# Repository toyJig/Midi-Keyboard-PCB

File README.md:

# Midi-Keyboard-PCB
A simple small MIDI Keyboard PCB designed for Half Life Hack Club with buttons, sliders, potentiometer and mcu.

View the PCB Here!:

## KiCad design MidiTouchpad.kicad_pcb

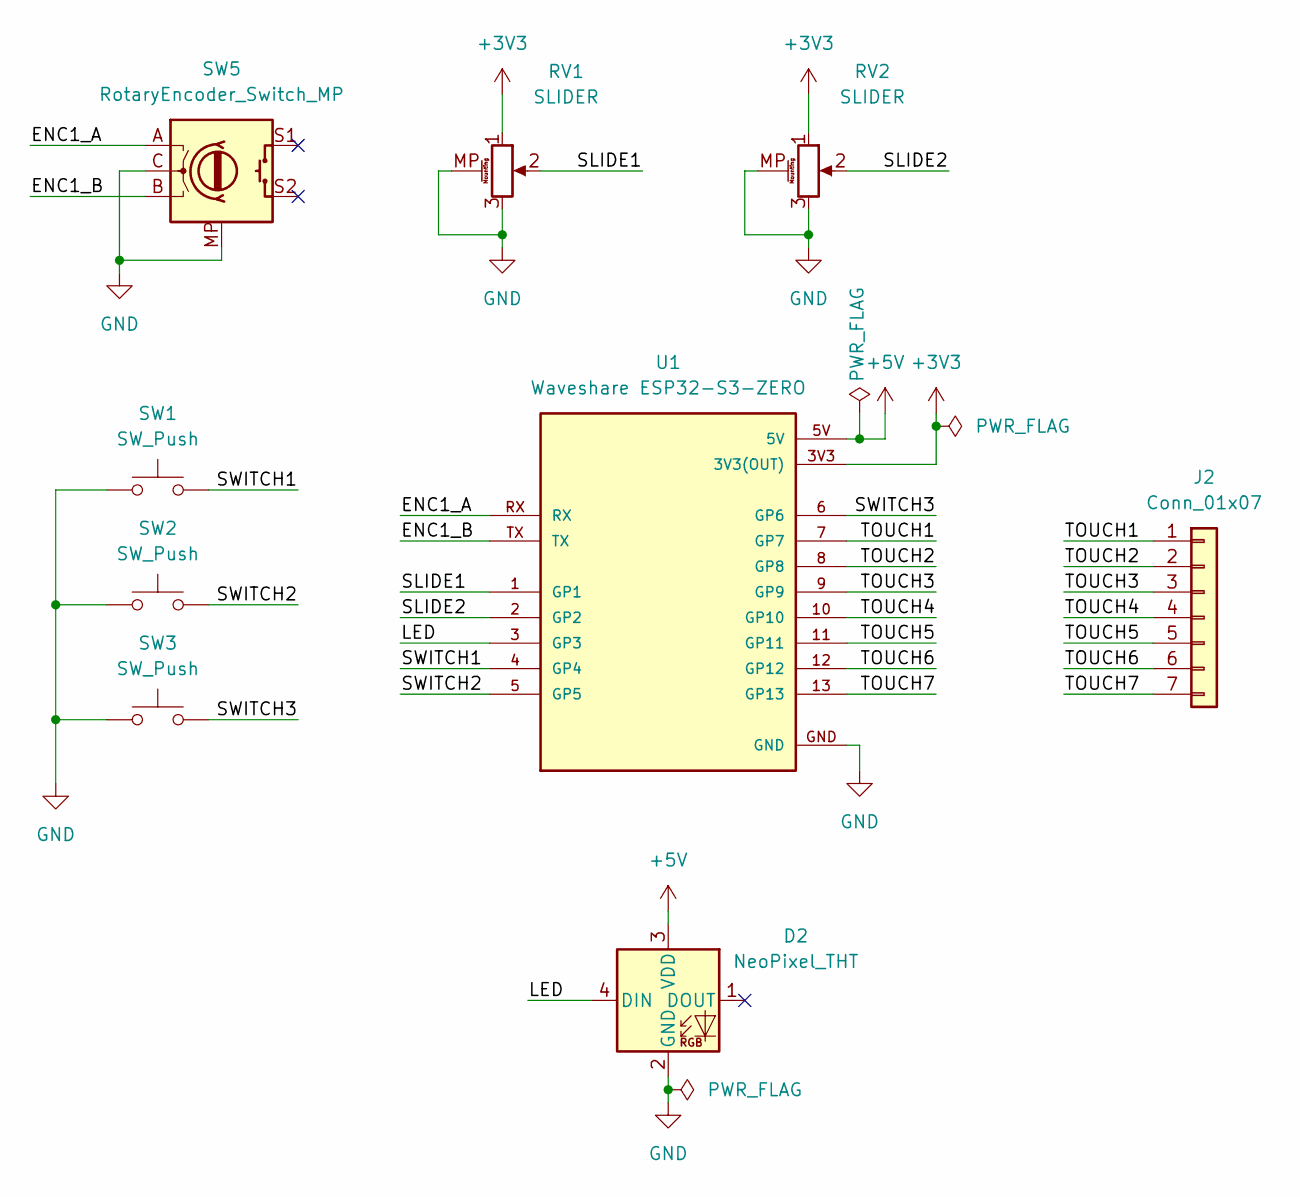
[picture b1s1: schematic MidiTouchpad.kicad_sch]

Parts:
D2: NeoPixel_THT; LED_SK6805_PLCC4_2.4x2.7mm_P1.3mm
J2: Conn_01x07
RV1, RV2: SLIDER; Potentiometer_Bourns_PTA1543_Single_Slide
SW1, SW2, SW3: SW_Push; Kailh Choc Low-Profile Switches
SW5: RotaryEncoder_Switch_MP; RotaryEncoder_Alps_EC11E-Switch_Vertical_H20mm
U1: Waveshare ESP32-S3-ZERO; Waveshare ESP32-S3-Zero; PARTREV NA

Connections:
+3V3: RV1.1, RV2.1, U1.3V3 (3V3(OUT))
+5V: D2.3 (VDD), U1.5V
/ENC1_A: SW5.A, U1.RX
/ENC1_B: SW5.B, U1.TX
/LED: D2.4 (DIN), U1.3 (GP3)
/SLIDE1: RV1.2, U1.1 (GP1)
/SLIDE2: RV2.2, U1.2 (GP2)
/SWITCH1: SW1.2, U1.4 (GP4)
/SWITCH2: SW2.2, U1.5 (GP5)
/SWITCH3: SW3.2, U1.6 (GP6)
/TOUCH1: J2.1, U1.7 (GP7)
/TOUCH2: J2.2, U1.8 (GP8)
/TOUCH3: J2.3, U1.9 (GP9)
/TOUCH4: J2.4, U1.10 (GP10)
/TOUCH5: J2.5, U1.11 (GP11)
/TOUCH6: J2.6, U1.12 (GP12)
/TOUCH7: J2.7, U1.13 (GP13)
GND: D2.2 (GND), RV1.3, RV1.MP (MountPin), RV2.3, RV2.MP (MountPin), SW1.1, SW2.1, SW3.1, SW5.C, SW5.MP, U1.GND

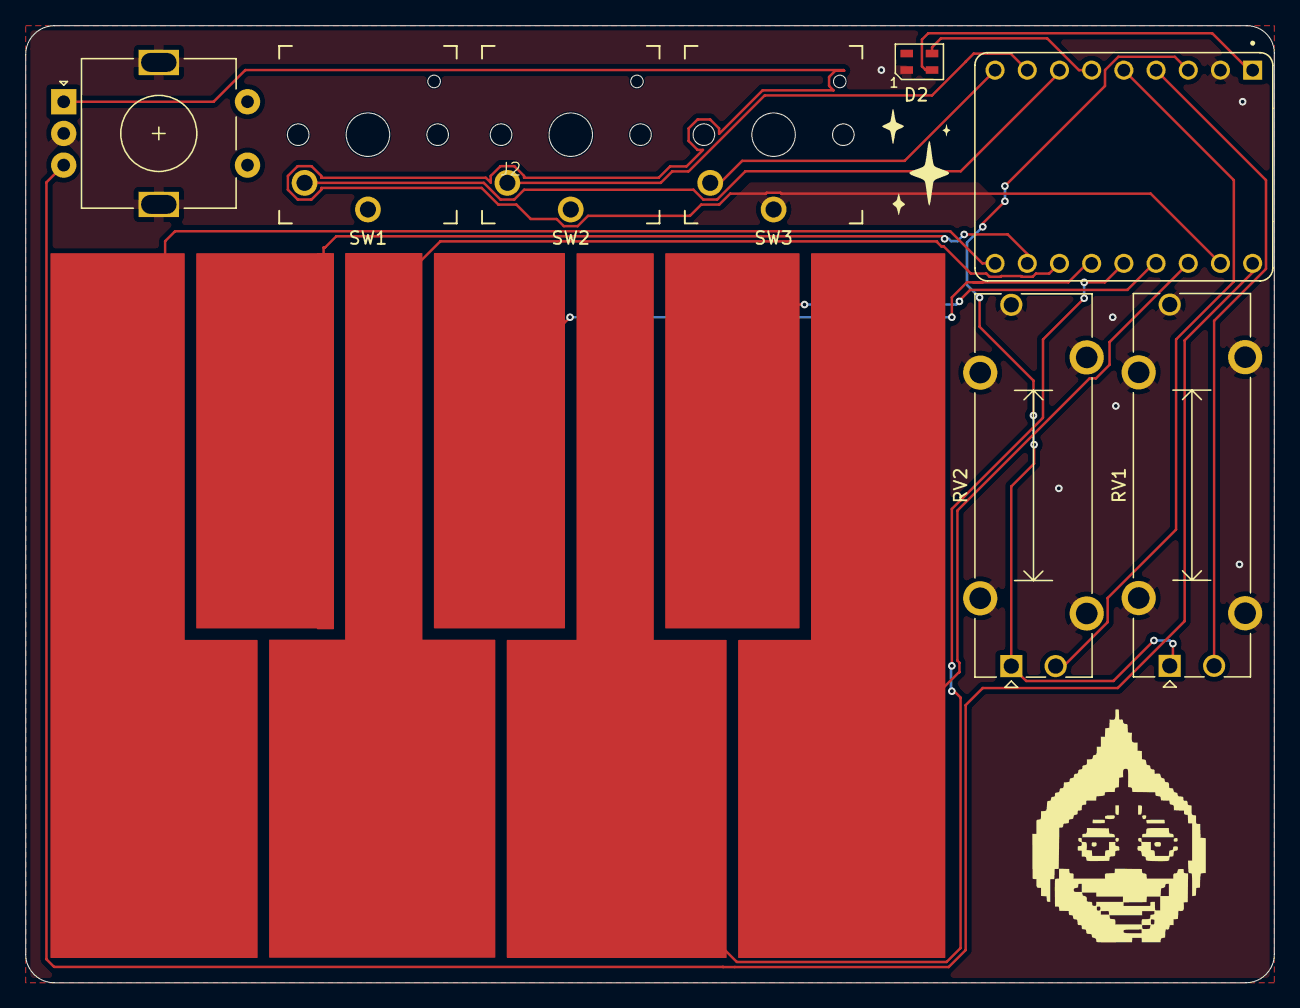
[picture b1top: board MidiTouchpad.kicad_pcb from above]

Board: 2 copper layers, 98.5 x 75.5 mm, 9 parts (0 on the bottom side), 18 nets.
